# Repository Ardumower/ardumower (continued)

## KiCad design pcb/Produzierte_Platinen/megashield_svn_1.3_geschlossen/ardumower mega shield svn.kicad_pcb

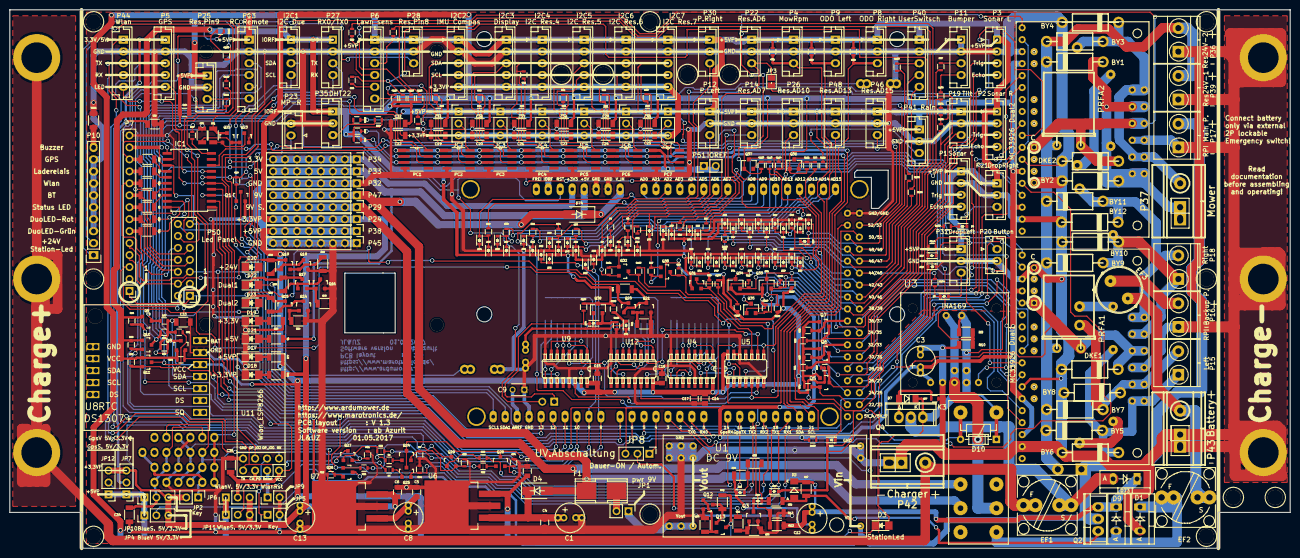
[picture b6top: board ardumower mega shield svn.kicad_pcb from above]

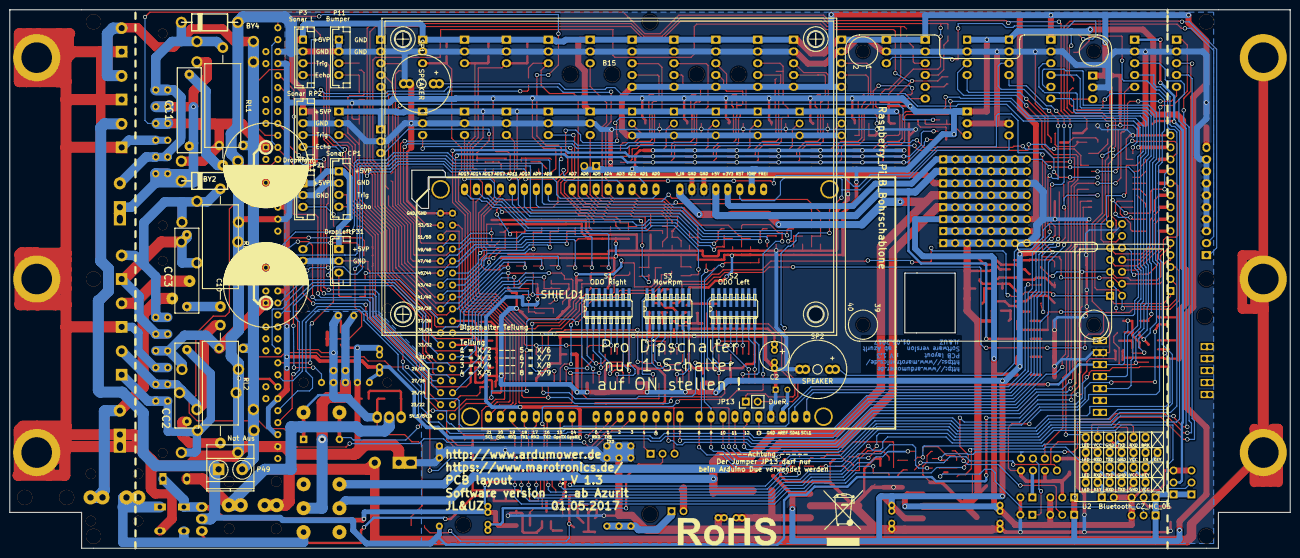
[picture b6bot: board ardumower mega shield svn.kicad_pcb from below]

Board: 2 copper layers, 271.8 x 114.3 mm, 442 parts (21 on the bottom side), 281 nets.

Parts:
B1, B2, B3, B4, B5, B6, B7, B8, B17, B18, B19, B20, B21, B22: Bohrloch_3,2mm
B9, B10, B11, B12, B13, B14: Bohrloch_6,5mm
B15: BumperDuino_Bohrschablone
B16: Raspberry_Pi_B_Bohrschablone; Raspberry_Pi_B_Bohrschablone_Rueckseite
B23: Mülleimer; WEEE-Logo_8.4x12mm_SilkScreen
B24: Rohos; RoHS-Logo_6mm_SilkScreen
BY1, BY2, BY3, BY4, BY5, BY6, BY7, BY8, BY9, BY10, BY11, BY12: BY 500/1000; Diode_liegend_BY500_1000_RM15
C1, C8, C13: 22uF; Elko_vert_11.2x6.3mm_RM2.5_RM5.0
C2: 47uF; Elko_vert_11.2x6.3mm_RM2.5_RM5.0
C3: 10uF; Elko_vert_11.2x6.3mm_RM2.5_RM5.0
C4, C5, C6, C7, C14, C15, C16, C17, C18: 100nF; C_0805
C9: 100nF; C_Disc_D3_P2.5
C10, C11: 2200uF 63V; C_Radial_D18_L36_P7.5
C12: 22uF / 63V; Elko_vert_11.2x6.3mm_RM2.5_RM5.0
C19, C20, C21, C22, C23, C24, C25, C26, C27, C28, C29, C30, C31, C32, C33, C34, C35, C36: 100nF; C_1206
CC1, CC2, CC3: MP3-Y2 10N; Kondensator_cnp_18x5mm
D1, D9: MBR 1045; Diode_TO-220_Vertical
D2, D7: SMD ZF 15; MiniMELF_Standard
D3: StationLed; LED_1206
D4, D74: S 1G SMD; D_SMA_Standard
D5, D6, D8, D11, D12, D13, D14, D15, D16, D24, D25, D26, D27, D28, D29, D30, D31, D32, D33, D34, D35, D36, D37, D38, D39, D40, D41, D42, D43, D44, D45, D46, D47, D48, D49, D50, D51, D52, D53, D54, D55, D56, D57, D58, D59, D60, D61, D62, D63, D64, D65, D66, D67, D68, D69, D70, D71, D72, D75, D76: TSS0230LU; D_0603
D10: 1N4148; D_DO-35_SOD27_P7.62mm_Horizontal
D17: +5VP; LED_1206
D18: +3,3VP; LED_1206
D19: +3,3V; LED_1206
D20: +24V; LED_1206
D21: +5V; LED_1206
D22: Dual1; LED_1206
D23: Dual2; LED_1206
D73: MBR 1045; MBR1045
DKE1, DKE2: 15KE33CA; Diode_liegend_BY500_1000_RM15
Dual1, Dual2: MC33926; MC_33926_31polig_mit_Bohrloch_neue_Masse_mit_zweite_Lochrei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
EF1: F_5A; Fuseholder5x20_vert_closed_Bulgin_FX0456_und_TR15_Halter
EF2: F_10A; Fuseholder5x20_vert_closed_Bulgin_FX0456_und_TR15_Halter
EF3: 1A; Sicherungs_Sockel_für_TR5_TE5
F1: PTC; Fuse_SMD
I2C1: I2C Due; JST_EH_B04B-EH-A_04x2.50mm_Straight
I2C2: IMU Compas; JST_EH_B05B-EH-A_05x2.50mm_Straight
I2C3: Display; JST_EH_B05B-EH-A_05x2.50mm_Straight
I2C4: I2C Res.4; JST_EH_B05B-EH-A_05x2.50mm_Straight
I2C5: I2C Res.5; JST_EH_B05B-EH-A_05x2.50mm_Straight
I2C6: I2C Res.6; JST_EH_B05B-EH-A_05x2.50mm_Straight
I2C7: I2C Res.7; JST_EH_B05B-EH-A_05x2.50mm_Straight
IC1: UDN 2987 LWTR-6T; SOIC-20W_7.5x12.8mm_Pitch1.27mm
JC2, JC3, JC4, JC5, JC6, JC7: JUMPER3; Pin_Header_Straight_1x03_Pitch2.54mm
JP1: pwr 9V; Pin_Header_Straight_1x02_Pitch2.54mm
JP2, JP5: Key; Pin_Header_Straight_1x02_Pitch2.54mm
JP3: M1FB; SJ
JP4: BlueV 5V/3.3V; Pin_Header_Straight_1x03_Pitch2.54mm
JP6: WlanV. 5V/3.3V; Pin_Header_Straight_1x03_Pitch2.54mm
JP7: GpsV 5V/3.3V; Pin_Header_Straight_1x03_Pitch2.54mm
JP8: UV.Abschaltung; Pin_Header_Straight_1x03_Pitch2.54mm
JP9: WlanRst; Pin_Header_Straight_1x02_Pitch2.54mm
JP10: BlueS. 5V/3.3V; Pin_Header_Straight_1x03_Pitch2.54mm
JP11: WlanS. 5V/3.3V; Pin_Header_Straight_1x03_Pitch2.54mm
JP12: GpsS. 5V/3.3V; Pin_Header_Straight_1x03_Pitch2.54mm
JP13: DueR.; Pin_Header_Straight_1x02_Pitch2.54mm
K3: RELAY_2RT; Relais_DPDT_Schrack-RT2_RM5mm_3D_Kontaktbelegung_geändert_F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
P1: Sonar C; JST_EH_B04B-EH-A_04x2.50mm_Straight
P2: Sonar R; JST_EH_B04B-EH-A_04x2.50mm_Straight
P3: Sonar L; JST_EH_B04B-EH-A_04x2.50mm_Straight
P4: MowRpm; JST_EH_B03B-EH-A_03x2.50mm_Straight
P5: GPS; JST_EH_B05B-EH-A_05x2.50mm_Straight
P6: Lawn sens; JST_EH_B06B-EH-A_06x2.50mm_Straight
P7: Status LEDs; Socket_Strip_Straight_1x14_Pitch2.54mm
P8: ODO Right; JST_EH_B03B-EH-A_03x2.50mm_Straight
P9: ODO Left; JST_EH_B03B-EH-A_03x2.50mm_Straight
P10: Status LEDs GND; Socket_Strip_Straight_1x10_Led_Bargraph_Anzeige
P11: Bumper; JST_EH_B04B-EH-A_04x2.50mm_Straight
P12: P.Left; JST_EH_B03B-EH-A_03x2.50mm_Straight
P13: RC Remote; JST_EH_B06B-EH-A_06x2.50mm_Straight
P14: Res.AD7; JST_EH_B03B-EH-A_03x2.50mm_Straight
P15: Left; TerminalBlock_Pheonix_MKDS1.5-2pol
P16: RPI Backup P.; TerminalBlock_Pheonix_MKDS1.5-2pol
P17: RPI Main P.; TerminalBlock_Pheonix_MKDS1.5-2pol
P18: Right; TerminalBlock_Pheonix_MKDS1.5-2pol
P19: Tilt; JST_EH_B03B-EH-A_03x2.50mm_Straight
P20: Button; JST_EH_B02B-EH-A_02x2.50mm_Straight
P21: DropRight; JST_EH_B03B-EH-A_03x2.50mm_Straight
P22: Res.AD6; JST_EH_B03B-EH-A_03x2.50mm_Straight
P23: MP-R; JST_EH_B02B-EH-A_02x2.50mm_Straight
P24: +3.3VP; Pin_Header_Straight_1x08_Pitch2.54mm
P25: Res.Pin9; JST_EH_B03B-EH-A_03x2.50mm_Straight
P26: Res.AD10; JST_EH_B03B-EH-A_03x2.50mm_Straight
P27: RX0/TX0; JST_EH_B04B-EH-A_04x2.50mm_Straight
P28: Res.Pin8; JST_EH_B03B-EH-A_03x2.50mm_Straight
P29: 9V S.; Pin_Header_Straight_1x08_Pitch2.54mm
P30: P.Right; JST_EH_B03B-EH-A_03x2.50mm_Straight
P31: DropLeft; JST_EH_B03B-EH-A_03x2.50mm_Straight
P32, P45: GND; Pin_Header_Straight_1x08_Pitch2.54mm
P33: 5V; Pin_Header_Straight_1x08_Pitch2.54mm
P34: 3,3V; Pin_Header_Straight_1x08_Pitch2.54mm
P35: DHT22; JST_EH_B03B-EH-A_03x2.50mm_Straight
P36: Res24V-2; TerminalBlock_Pheonix_MKDS1.5-2pol
P37: Mower; Anschlussklemme_RM5,08-RM7,62
P38: +5VP; Pin_Header_Straight_1x08_Pitch2.54mm
P39: Res24V-1; TerminalBlock_Pheonix_MKDS1.5-2pol
P40: UserSwitsch; JST_EH_B05B-EH-A_05x2.50mm_Straight
P41: Rain; JST_EH_B03B-EH-A_03x2.50mm_Straight
P42: Charger; Anschlussklemme_RM5,08-RM7,62
P43: Battery; Anschlussklemme_RM5,08-RM7,62
P44: Wlan; JST_EH_B05B-EH-A_05x2.50mm_Straight
P46: Res.AD15; JST_EH_B03B-EH-A_03x2.50mm_Straight
P47: 9V; Pin_Header_Straight_1x08_Pitch2.54mm
P48: Res.AD13; JST_EH_B03B-EH-A_03x2.50mm_Straight
P49: Not Aus; TerminalBlock_Pheonix_MKDS1.5-2pol
P50: Led Panel; Pin_Header_Straight_2x07_Pitch2.54mm
P51: IOREF; Socket_Strip_Straight_1x02_Pitch2.54mm
PC1, PC2, PC3, PC4, PC5, PC6, PC7: PCA9517D; SOIC127P600X175-8N
PRFA1, PRFA2: PFRA 500; PRFA_500
Q1, Q24, Q25, Q26, Q27, Q28, Q29, Q38: BC847B; SOT-23
Q2, Q4: IRF9540N; TO-220
Q3, Q12, Q13, Q14, Q15, Q16, Q17, Q18, Q19, Q20, Q21, Q22, Q23: BC817; SOT-23
Q5, Q6, Q7, Q8, Q9, Q10, Q11, Q30, Q31, Q32, Q33, Q34, Q35, Q36, Q37: BSS138; SOT-23
R1, R2, R5, R17, R20, R21, R22, R25, R77, R134: 220R; R_1206
R3, R4, R26, R27, R29, R50, R54, R82, R83, R84, R85, R86, R87, R88, R89, R90, R103, R104, R105, R106, R107, R108, R109, R110, R111, R112: 300R; R_0603
R6, R7, R16, R28, R30, R31, R92, R93, R96: 4K7; R_0603
R8, R14, R15, R39, R42, R46, R49, R51, R52, R53, R55, R56, R58, R59, R60, R61, R62, R63, R64, R65, R66, R67, R68, R69, R70, R71, R91, R94, R95, R97, R98, R99, R100, R101, R102, R113, R114, R115, R116, R117, R118, R119, R120, R121, R122, R123, R124, R131, R132, R133, R137: 10K; R_0603
R9, R12: 100K 0,1%; R_1206
R10, R13: 10K 0,1%; R_1206
R11, R73, R79: 68R; R_1206
R18, R43: 2k2; R_0603
R19, R38, R72, R74, R76, R81: 8K2; R_1206
R23, R33, R78: 100R; R_1206
R24, R75, R80: 180R; R_1206
R32: 1K; R_1206
R34, R35: 10K; R_1206
R36: 30K; R_1206
R37: 100K; R_1206
R40, R41, R44, R45, R47, R48, R125, R126, R127, R128, R129, R130: XXXX; R_0603
R57: 100K; R_0603
R135: 56K; R_0603
R136: 1K; R_0603
RL1, RL2, RL3: 1,8R 2W METALL; Resistor_Horizontal_RM25mm-2W
S1: ODO Right; SW_DIP_x8_SMD
S2: ODO Left; SW_DIP_x8_SMD
S3: MowRpm; SW_DIP_x8_SMD
SHIELD1: ARDUINO_MEGA_SHIELD; ARDUINO_MEGA_SHIELD_DUO_3D
SP1, SP2: SPEAKER; Buzzer_12x9.5RM7.6_RM5.0
U1: DC 9V; DC_DC_DSN2596_mit_Bohrloch_doppelte_Lochreihe
U2: Bluetooth_CZ_HC_05; Bluetooth_Buchse_Platz_mit_Beschriftung_4_fach
U3: INA169
U4, U9, U12: 4017; 40xx-SO16
U5: 4081; 40xx-SO14
U6: LM2940CS-5.0; TO-263-3Lead
U7: LM3940IS-3.3; TO-263-3Lead
U8: DS1307+; Tiny_RTC_DS1307_geändert_mit_Bohrloch_4Lochreihen
U11: Wlan_ESP8266; Wlan_ESP8266_3D_mit_Pin_Beschreibung_ohne_Rahmen

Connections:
9Vgeschaltet: K3.3, P29.1, P29.2, P29.3, P29.4, P29.5, P29.6, P29.7, P29.8
+3.3VP: C6.1, C13.1, I2C2.5, I2C3.5, I2C4.5, I2C5.5, I2C6.5, I2C7.5, JC2.3, JC3.3, JC4.3, JC5.3, JC6.3, JC7.3, JP2.2, JP4.3, JP6.3, JP7.3, JP10.3, JP11.3, JP12.3, P24.1, P24.2, P24.3, P24.4, P24.5, P24.6, P24.7, P24.8, R78.1, U7.3
+3V3: P34.1, P34.2, P34.3, P34.4, P34.5, P34.6, P34.7, P34.8, R23.1, SHIELD1.3V3
+5V: P33.1, P33.2, P33.3, P33.4, P33.5, P33.6, P33.7, P33.8, R1.1, SHIELD1.5V
+5VP: C5.1, C7.1, C8.1, C14.1, C15.1, C16.1, C17.1, C18.1, C22.1, C33.1, I2C2.1, I2C3.1, I2C4.1, I2C5.1, I2C6.1, I2C7.1, IC1.11, JC2.1, JC3.1, JC4.1, JC5.1, JC6.1, JC7.1, JP4.1, JP6.1, JP7.1, JP10.1, JP11.1, JP12.1, P1.1, P2.1, P3.1, P4.1, P6.1, P8.1, P9.1, P12.1, P13.1, P14.1, P19.1, P21.1, P22.1, P25.1, P26.1, P28.1, P30.1, P31.1, P38.1, P38.2, P38.3, P38.4, P38.5, P38.6, P38.7, P38.8, P40.1, P41.1, P46.1, P48.1, PC1.8, R28.2, R30.2, R31.1, R43.1, R59.1, R61.1, R63.1, R65.1, R67.1, R69.1, R71.1, R77.1, R98.1, R100.1, R102.1, R116.1, R118.1, R120.1, R122.1, R124.1, U4.16, U5.14, U6.3, U7.1, U8.3, U9.16, U12.16
+9V: D4.2, D74.2, F1.2, K3.5, P47.1, P47.2, P47.3, P47.4, P47.5, P47.6, P47.7, P47.8
+24V: D20.2, P7.5, P17.2, P49.1, P50.5, Q2.2, U1.3
/Anschlußstecker/LShifter1/5V_IN: P1.4, Q5.3, R59.2
/Anschlußstecker/LShifter2/5V_IN: P2.4, Q6.3, R61.2
/Anschlußstecker/LShifter3/5V_IN: P3.4, Q7.3, R63.2
/Anschlußstecker/LShifter4/5V_IN: P13.3, Q8.3, R65.2
/Anschlußstecker/LShifter5/5V_IN: P13.4, Q9.3, R67.2
/Anschlußstecker/LShifter6/5V_IN: P13.5, Q10.3, R69.2
/Anschlußstecker/LShifter7/5V_IN: P13.6, Q11.3, R71.2
/Anschlußstecker/LShifter8/5V_IN: Q30.3, R98.2, U5.10
/Anschlußstecker/LShifter9/5V_IN: Q31.3, R100.2, U5.4
/Anschlußstecker/LShifter10/5V_IN: Q32.3, R102.2, U5.3
/Anschlußstecker/LShifter11/5V_IN: P3.3, Q33.3, R116.2
/Anschlußstecker/LShifter12/5V_IN: P2.3, Q34.3, R118.2
/Anschlußstecker/LShifter13/5V_IN: P1.3, Q35.3, R120.2
/Anschlußstecker/LShifter14/5V_IN: P41.3, Q36.3, R122.2
/Anschlußstecker/LShifter15/5V_IN: P19.3, Q37.3, R124.2
/Anschlußstecker/OdoTeiler/Eingang1: P8.3, R28.1, U4.14, U5.1
/Anschlußstecker/OdoTeiler/Eingang2: P9.3, R30.1, U5.5, U9.14
/Anschlußstecker/OdoTeiler/Eingang3: P4.3, R31.2, U5.8, U12.14
/Motortreiber/+24V: BY1.1, BY3.1, BY5.1, BY7.1, BY9.1, BY11.1, P36.2, P39.2, P49.2, PRFA1.1, PRFA2.1
/Motortreiber/MotorLinks/MotorIN1: BY5.2, BY6.1, CC2.1, Dual1.19, P15.1
/Motortreiber/MotorLinks/MotorIN2: BY7.2, BY8.1, Dual1.20, P15.2, RL2.2
/Motortreiber/MotorRechts/MotorIN1: BY9.2, BY10.1, CC3.1, Dual1.23, P18.1
/Motortreiber/MotorRechts/MotorIN2: BY11.2, BY12.1, Dual1.24, P18.2, RL3.2
/Motortreiber/MähmotorSchutz/MotorIN1: BY1.2, BY2.1, CC1.1, Dual2.19, Dual2.23, P37.1
/Motortreiber/MähmotorSchutz/MotorIN2: BY3.2, BY4.1, Dual2.20, Dual2.24, P37.2, RL1.2
/USpannungAB/Batterieeingang 24V: C12.1, D2.1, D9.1, D73.1, Q2.3, R12.1, R37.1
/VerpolungsschutzLade./Eingang: D73.2, EF1.2, Q4.2
Charg_Pin_+: B9.1, B10.1, B11.1, EF1.1, P42.2
DHT22: P35.3, R39.2, R109.1
DropLeft: D5.1, P31.3
DropRight: D6.1, P21.3
Dual1: C10.1, D22.2, DKE1.1, Dual1.22, PRFA1.2
Dual2: C11.1, D23.2, DKE2.1, Dual2.22, PRFA2.2
DuoLED-Rot: IC1.2, SHIELD1.7
DuoLED_Grün: IC1.1, SHIELD1.6
GND: B12.1, B13.1, B14.1, BY2.2, BY4.2, BY6.2, BY8.2, BY10.2, BY12.2, C1.2, C2.2, C3.2, C4.2, C5.2, C6.2, C7.2, C8.2, C9.1, C10.2, C11.2, C13.2, C14.2, C15.2, C16.2, C17.2, C18.2, C19.2, C20.2, C21.2, C22.2, C23.2, C24.2, C25.2, C26.2, C27.2, C28.2, C29.2, C30.2, C31.2, C32.2, C33.2, C34.2, C35.2, C36.2, D1.2, D16.2, D17.1, D18.1, D19.1, D21.1, D24.2, D25.2, D27.2, D30.2, D34.2, D35.2, D36.2, D38.2, D40.2, D42.2, D44.2, D46.2, D48.2, D50.2, D52.2, D54.2, D56.2, D58.2, D60.2, D62.2, D64.2, D66.2, D68.2, D70.2, D72.2, D75.2, DKE1.2, DKE2.2, Dual1.2, Dual1.7, Dual1.16, Dual1.21, Dual2.2, Dual2.7, Dual2.16, Dual2.21, I2C1.2, I2C2.2, I2C3.2, I2C4.2, I2C5.2, I2C6.2, I2C7.2, IC1.12, JP5.2, JP9.2, P1.2, P2.2, P3.2, P4.2, P5.2, P6.2, P7.14, P8.2, P9.2, P10.3, P10.4, P10.5, P10.6, P10.7, P10.8, P10.9, P11.1, P11.2, P12.2, P13.2, P14.2, P16.1, P17.1, P19.2, P20.2, P21.2, P22.2, P23.2, P25.2, P26.2, P27.2, P28.2, P30.2, P31.2, P32.1, P32.2, P32.3, P32.4, P32.5, P32.6, P32.7, P32.8, P35.2, P36.1, P39.1, P40.2, P41.2, P42.1, P43.1, P44.2, P45.1, P45.2, P45.3, P45.4, P45.5, P45.6, P45.7, P45.8, P46.2, P48.2, P50.14, PC1.4, PC2.4, PC3.4, PC4.4, PC5.4, PC6.4, PC7.4, Q1.2, Q3.2, Q12.2, Q14.2, Q16.2, Q18.2, Q21.2, Q23.2, R8.2, R10.2, R11.2, R13.2, R14.2, R15.2, R24.2, R35.2, R57.2, R73.2, R75.2, R79.2, R80.2, R91.2, R94.2, R95.2, R134.2, R136.2, SHIELD1.GND1, SHIELD1.GND2, SHIELD1.GND3, SHIELD1.GND4, SHIELD1.GND5, SP1.1, SP2.1, U1.1, U1.4, U2.GND, U3.2, U4.8, U4.13, U5.7, U5.12, U5.13, U6.2, U6.4, U7.2, U7.4, U8.2, U9.8, U9.13, U11.GND, U12.8, U12.13
GPS-LED: IC1.7, P5.5
GPS_RX: Q28.2, R94.1, SHIELD1.14
GPS_TX: R96.2, SHIELD1.15
IOREF: C3.1, C26.1, C27.1, C28.1, C29.1, C30.1, C31.1, C32.1, D8.1, D11.1, D26.1, D28.1, D29.1, D31.1, D32.1, D33.1, D37.1, D39.1, D41.1, D43.1, D45.1, D47.1, D49.1, D51.1, D53.1, D55.1, D57.1, D59.1, D61.1, D63.1, D65.1, D67.1, D69.1, D71.1, Dual1.3, Dual1.6, Dual1.15, Dual2.3, Dual2.6, Dual2.15, I2C1.1, JP8.3, P27.1, P35.1, P51.1, P51.2, PC1.1, PC2.1, PC3.1, PC4.1, PC5.1, PC6.1, PC7.1, Q5.1, Q6.1, Q7.1, Q8.1, Q9.1, Q10.1, Q11.1, Q24.3, Q25.3, Q28.3, Q30.1, Q31.1, Q32.1, Q33.1, Q34.1, Q35.1, Q36.1, Q37.1, Q38.3, R39.1, R47.1, R48.1, R58.1, R60.1, R62.1, R64.1, R66.1, R68.1, R70.1, R97.1, R99.1, R101.1, R113.2, R114.2, R115.1, R117.1, R119.1, R121.1, R123.1, R125.2, R126.2, R127.2, R128.2, R129.2, R130.2, R131.2, R132.2, R133.2, R135.1, R137.2, SHIELD1.IORE, U3.1
Led-BT: IC1.4, U2.LED
Led-Status: IC1.3, SHIELD1.13
Led-Wlan: IC1.5, P44.5, U11.GP_2
unnamed: C1.1, C4.1, D4.1, U6.1
unnamed: C2.1, D75.1, Q38.1, R135.2
unnamed: C9.2, SHIELD1.AREF
unnamed: C12.2, D12.2, R34.1
unnamed: C19.1, JC2.2, PC2.8, R40.1, R44.1
unnamed: C20.1, JC3.2, PC3.8, R41.1, R45.1
unnamed: C21.1, JC4.2, PC4.8, R42.1, R46.1
unnamed: C23.1, JC5.2, PC5.8, R51.1, R55.1
unnamed: C24.1, JC6.2, PC6.8, R52.1, R56.1
unnamed: C25.1, JC7.2, PC7.8, R49.1, R53.1
unnamed: C34.1, JP4.2, U2.VCC
unnamed: C35.1, JP6.2, P44.1, U11.CH_P, U11.VCC
unnamed: C36.1, JP7.2, P5.1
unnamed: CC1.2, RL1.1
unnamed: CC2.2, RL2.1
unnamed: CC3.2, RL3.1
unnamed: D1.1, D9.2, EF2.1, K3.16
unnamed: D2.2, Q2.1, R32.2, R37.2
unnamed: D3.1, Q13.3, R72.1
unnamed: D5.2, R104.1
unnamed: D6.2, R103.1
unnamed: D7.2, Q4.1, R57.1
unnamed: D10.2, K3.9, Q1.3
unnamed: D11.2, D24.1, R3.2, SHIELD1.AD5
unnamed: D12.1, R33.1, R34.2
unnamed: D13.2, D15.2, R32.1, R33.2
unnamed: D15.1, Q3.3
unnamed: D8.2, D16.1, R4.2, SHIELD1.AD4
unnamed: D17.2, R77.2
unnamed: D18.2, R78.2
unnamed: D19.2, R23.2
unnamed: D20.1, Q19.3, R76.1
unnamed: D21.2, R1.2
unnamed: D22.1, Q17.3, R38.1
unnamed: D23.1, Q15.3, R19.1
unnamed: D25.1, D26.2, R103.2, R114.1, SHIELD1.23
unnamed: D27.1, D28.2, R110.2, SHIELD1.35
unnamed: D29.2, D30.1, R87.2, R132.1, SHIELD1.38
unnamed: D31.2, D34.1, R105.2, R131.1, SHIELD1.39
unnamed: D32.2, D35.1, R111.2, R129.1, SHIELD1.9
unnamed: D33.2, D36.1, R112.2, R130.1, SHIELD1.8
unnamed: D37.2, D38.1, R29.2, R126.1, SHIELD1.40
unnamed: D39.2, D40.1, R54.2, R125.1, SHIELD1.41
unnamed: D41.2, D42.1, R83.2, R128.1, SHIELD1.42
unnamed: D43.2, D44.1, R85.2, R127.1, SHIELD1.43
unnamed: D45.2, D46.1, R86.2, SHIELD1.44
unnamed: D47.2, D48.1, R104.2, R113.1, SHIELD1.45
unnamed: D49.2, D50.1, R108.2, SHIELD1.47
unnamed: D51.2, D52.1, R106.2, SHIELD1.46
unnamed: D53.2, D54.1, R26.2, SHIELD1.AD7
unnamed: D55.2, D56.1, R82.2, SHIELD1.AD6
unnamed: D57.2, D58.1, R109.2, SHIELD1.49
unnamed: D59.2, D60.1, R84.2, SHIELD1.AD2
unnamed: D61.2, D62.1, R107.2, SHIELD1.48
unnamed: D63.2, D64.1, R90.2, SHIELD1.AD8
unnamed: D65.2, D66.1, R27.2, SHIELD1.AD15
unnamed: D67.2, D68.1, R89.2, SHIELD1.AD9
unnamed: D69.2, D70.1, R50.2, SHIELD1.AD13
unnamed: D71.2, D72.1, R88.2, SHIELD1.AD10
unnamed: D74.1, SHIELD1.V_IN
unnamed: D76.1, Q38.2, R136.1
unnamed: D76.2, JP13.1, R137.1
unnamed: Dual2.9, JP3.2
unnamed: EF2.2, EF3.1, P43.2
unnamed: EF3.2, P16.2
unnamed: F1.1, JP1.2
unnamed: IC1.10, R43.2
unnamed: IC1.13, P7.13, P50.13, SP1.2, SP2.2
unnamed: IC1.14, R25.1
unnamed: IC1.15, R17.1
unnamed: IC1.16, R22.1
unnamed: IC1.17, R2.1
unnamed: IC1.18, R5.1
unnamed: IC1.19, R20.1
unnamed: IC1.20, R21.1
unnamed: JP1.1, U1.2
unnamed: JP2.1, U2.Key
unnamed: JP5.1, U11.GP_0
unnamed: JP8.2, R36.2
unnamed: JP9.1, U11.Rese
unnamed: JP10.2, Q26.3
unnamed: JP11.2, Q27.3
unnamed: JP12.2, Q29.3
unnamed: K3.12, U3.5
unnamed: P5.3, R93.2
unnamed: P5.4, Q29.2, R95.1
unnamed: P7.2, P10.1, P50.2, Q22.3, R81.1
unnamed: P7.3, P10.2, P50.3, Q20.3, R74.1
unnamed: P10.10, R134.1
unnamed: P44.3, R7.2, U11.TX
unnamed: P44.4, Q27.2, R91.1, U11.RX
unnamed: P7.6, P50.6, R21.2
unnamed: P7.7, P50.7, R20.2
unnamed: P7.8, P50.8, R5.2
unnamed: P7.9, P50.9, R2.2
unnamed: P7.10, P50.10, R22.2
unnamed: P7.11, P50.11, R17.2
unnamed: P7.12, P50.12, R25.2
unnamed: Q1.1, R18.2
unnamed: Q3.1, R35.1, R36.1
unnamed: Q12.1, Q13.2, R73.1
unnamed: Q12.3, Q13.1, R72.2
unnamed: Q14.1, Q15.2, R24.1
unnamed: Q14.3, Q15.1, R19.2
unnamed: Q16.1, Q17.2, R75.1
unnamed: Q16.3, Q17.1, R38.2
unnamed: Q18.1, Q19.2, R80.1
unnamed: Q18.3, Q19.1, R76.2
unnamed: Q20.1, Q21.3, R74.2
unnamed: Q20.2, Q21.1, R11.1
unnamed: Q22.1, Q23.3, R81.2
unnamed: Q22.2, Q23.1, R79.1
unnamed: Q24.1, R6.1
unnamed: Q25.1, R7.1
unnamed: Q26.1, R16.1
unnamed: Q26.2, R15.1, U2.RXD
unnamed: Q27.1, R92.1
unnamed: Q28.1, R93.1
unnamed: Q29.1, R96.1
unnamed: R6.2, U2.TXD
unnamed: S1.1, U4.4
unnamed: S1.2, U4.7
unnamed: S1.3, U4.10
unnamed: S1.4, U4.1
unnamed: S1.5, U4.5
unnamed: S1.6, U4.6
unnamed: S1.7, U4.9
unnamed: S1.8, U4.11
unnamed: S1.9, S1.10, S1.11, S1.12, S1.13, S1.14, S1.15, S1.16, U4.15
unnamed: S2.1, U9.4
unnamed: S2.2, U9.7
unnamed: S2.3, U9.10
unnamed: S2.4, U9.1
unnamed: S2.5, U9.5
unnamed: S2.6, U9.6
unnamed: S2.7, U9.9
unnamed: S2.8, U9.11
unnamed: S2.9, S2.10, S2.11, S2.12, S2.13, S2.14, S2.15, S2.16, U9.15
unnamed: S3.1, U12.4
unnamed: S3.2, U12.7
unnamed: S3.3, U12.10
unnamed: S3.4, U12.1
unnamed: S3.5, U12.5
unnamed: S3.6, U12.6
unnamed: S3.7, U12.9
unnamed: S3.8, U12.11
unnamed: S3.9, S3.10, S3.11, S3.12, S3.13, S3.14, S3.15, S3.16, U12.15
unnamed: U4.2, U5.2
unnamed: U5.6, U9.2
unnamed: U5.9, U12.2
RX0: P27.3, SHIELD1.0
RX1: Q25.2, R14.1, SHIELD1.19
RX2: Q24.2, R8.1, SHIELD1.17
RelaisAbschaltung: JP8.1, SHIELD1.4
ReserveAD6: JP3.1, P22.3, R82.1
ReserveAD7: P14.3, R26.1
ReserveAD10: P26.3, R88.1
ReservePin8: P28.3, R112.1
ReservePin9: P25.3, R111.1
Reset: JP13.2, P23.1, SHIELD1.RST
Resv.PinAD13: P48.3, R50.1
Resv.PinAD15: P46.3, R27.1
SCL: PC1.2, PC2.2, PC3.2, PC4.2, PC5.2, PC6.2, PC7.2, R48.2, SHIELD1.21
SCL1: PC1.7, U8.5
SCL2: I2C2.4, PC2.7, R44.2
SCL3: I2C3.4, PC3.7, R45.2
SCL4: I2C4.4, PC4.7, R46.2
SCL5: I2C5.4, PC5.7, R51.2
SCL6: I2C6.4, PC6.7, R52.2
SCL7: I2C7.4, PC7.7, R49.2
SCL22: I2C1.4, SHIELD1.SCL1
SDA: PC1.3, PC2.3, PC3.3, PC4.3, PC5.3, PC6.3, PC7.3, R47.2, SHIELD1.20
SDA1: PC1.6, U8.4
SDA2: I2C2.3, PC2.6, R40.2
SDA3: I2C3.3, PC3.6, R41.2
SDA4: I2C4.3, PC4.6, R42.2
SDA5: I2C5.3, PC5.6, R55.2
SDA6: I2C6.3, PC6.6, R56.2
SDA7: I2C7.3, PC7.6, R53.2
SDA22: I2C1.3, SHIELD1.SDA1
StationLed: D3.2, D7.1, D10.1, K3.8, P7.4, P50.4, Q4.3, R9.1, U3.4
TX0: P27.4, SHIELD1.1
TX1: R92.2, SHIELD1.18
TX2: R16.2, SHIELD1.16
Taster: D13.1, D14.1, P7.1, P20.1, P50.1
pinBatteryVoltage: R12.2, R13.1, R84.1
pinBumperLeft: P11.4, R105.1
pinBumperRight: P11.3, R87.1
pinButton: D14.2, R133.1, SHIELD1.51
pinBuzzer: IC1.8, SHIELD1.53
pinChargeCurrent: R90.1, U3.3
pinChargeVoltage: R9.2, R10.1, R89.1
pinChargingEnable: IC1.6, R18.1, SHIELD1.50
pinLawnBackRecv: P6.6, R83.1
pinLawnBackSend: P6.5, R85.1
pinLawnFrontRecv: P6.4, R29.1
pinLawnFrontSend: P6.3, R54.1
pinMotorEnable: Dual1.10, SHIELD1.37
pinMotorLeftDir: Dual1.4, SHIELD1.31
pinMotorLeftFault: Dual1.8, SHIELD1.25
pinMotorLeftPWM: Dual1.5, SHIELD1.5
pinMotorLeftSense: Dual1.9, SHIELD1.AD1
pinMotorMowDir: Dual2.4, Dual2.13, SHIELD1.29
pinMotorMowEnable: Dual2.10, SHIELD1.28
pinMotorMowFault: Dual2.8, Dual2.17, SHIELD1.26
pinMotorMowPWM: Dual2.5, Dual2.14, SHIELD1.2
pinMotorMowRpm_neu: Q30.2, R97.2, SHIELD1.AD11
pinMotorMowSense: Dual2.18, SHIELD1.AD3
pinMotorRightDir: Dual1.13, SHIELD1.33
pinMotorRightFault: Dual1.17, SHIELD1.27
pinMotorRightPWM: Dual1.14, SHIELD1.3
pinMotorRightSense: Dual1.18, SHIELD1.AD0
pinOdometryLeft: Q31.2, R99.2, SHIELD1.AD12
pinOdometryRight: Q32.2, R101.2, SHIELD1.AD14
pinPerimeterLeft: P12.3, R3.1
pinPerimeterRight: P30.3, R4.1
pinRain: Q36.2, R86.1, R121.2
pinRemoteMow: Q8.2, R64.2, SHIELD1.12
pinRemoteSpeed: Q10.2, R68.2, SHIELD1.10
pinRemoteSteer: Q9.2, R66.2, SHIELD1.11
pinRemoteSwitch: Q11.2, R70.2, SHIELD1.52
pinSonarCenterEcho: Q5.2, R58.2, SHIELD1.22
pinSonarCenterTrigger: Q35.2, R119.2, SHIELD1.24
pinSonarLeftEcho: Q7.2, R62.2, SHIELD1.36
pinSonarLeftTrigger: Q33.2, R115.2, SHIELD1.34
pinSonarRightEcho: Q6.2, R60.2, SHIELD1.32
pinSonarRightTrigger: Q34.2, R117.2, SHIELD1.30
pinTilt: Q37.2, R110.1, R123.2
pinUserSwitch1: P40.5, R106.1
pinUserSwitch2: P40.4, R108.1
pinUserSwitch3: P40.3, R107.1

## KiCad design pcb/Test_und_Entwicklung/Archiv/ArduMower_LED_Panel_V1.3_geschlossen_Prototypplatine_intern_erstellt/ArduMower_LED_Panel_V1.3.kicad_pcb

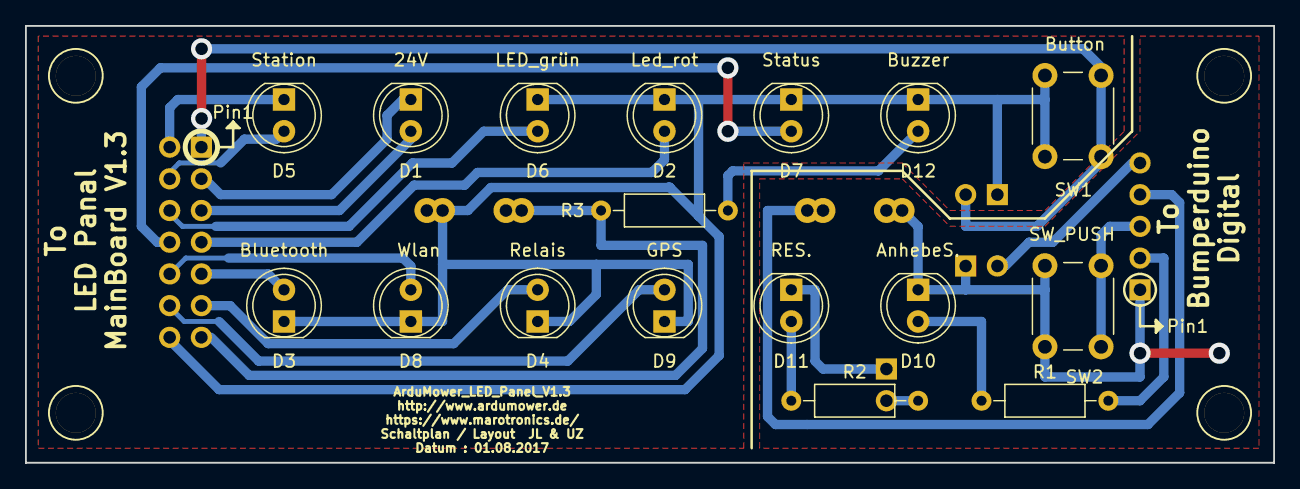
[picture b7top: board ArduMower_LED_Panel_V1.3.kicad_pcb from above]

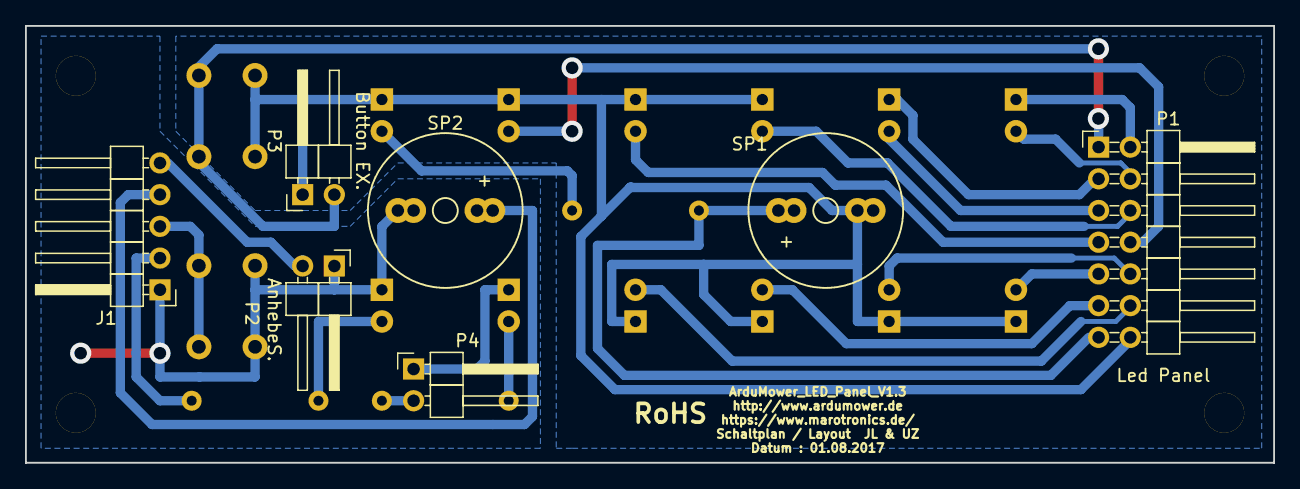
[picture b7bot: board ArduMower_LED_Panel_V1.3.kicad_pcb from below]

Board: 2 copper layers, 100.0 x 35.0 mm, 28 parts (7 on the bottom side), 24 nets.

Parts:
B1, B2, B3, B4: Bohrloch_3,2mm_ohne_Kupferfläche; Bohrloch_3,2mm
D1: 24V; LED_D5.0mm
D2: Led_rot; LED_D5.0mm
D3: Bluetooth; LED_D5.0mm
D4: Relais; LED_D5.0mm
D5: Station; LED_D5.0mm
D6: LED_grün; LED_D5.0mm
D7: Status; LED_D5.0mm
D8: Wlan; LED_D5.0mm
D9: GPS; LED_D5.0mm
D10: AnhebeS.; LED_D5.0mm
D11: RES.; LED_D5.0mm
D12: Buzzer; LED_D5.0mm
J1: CONN_01X05; Pin_Header_Angled_1x05_Pitch2.54mm
P1: Led Panel; Pin_Header_Angled_2x07_Pitch2.54mm
P2: AnhebeS.; Pin_Header_Angled_1x02_Pitch2.54mm
P3: Button EX.; Pin_Header_Angled_1x02_Pitch2.54mm
P4: RES.; Pin_Header_Angled_1x02_Pitch2.54mm
R1, R2, R3: 220; R_Axial_DIN0207_L6.3mm_D2.5mm_P10.16mm_Horizontal
SP1: Buzzer; Buzzer_12x9.5RM7.6_RM5.0
SP2: SPEAKER; Buzzer_12x9.5RM7.6_RM5.0
SW1: Button; SW_PUSH_6mm_h8.5mm
SW2: SW_PUSH; SW_PUSH_6mm_h8.5mm

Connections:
/24V: D1.2, P1.5
/24V_GND: D1.1, P1.3
/Bluetooth: D3.2, P1.9
/Buzzer: P1.13, R3.2, SP1.2
/Duo_Led_Rot: D2.2, P1.7
/Duo_Led_grün: D6.2, P1.6
/GPS_LED: D9.2, P1.12
/Led_Status: D7.2, P1.8
/PinCharging_Enable: D4.2, P1.11
/StationLed: D5.2, P1.4
/StationLed_GND: D5.1, P1.2
/Taster: P1.1, P3.2, SW1.2
/Wlan: D8.2, P1.10
GND: D2.1, D3.1, D4.1, D6.1, D7.1, D8.1, D9.1, D12.1, P1.14, P3.1, SP1.1, SW1.1
GNDD: D10.1, J1.1, P2.1, SP2.1, SW2.1
unnamed: D10.2, R1.1
unnamed: D11.1, P4.1
unnamed: D11.2, R2.1
unnamed: D12.2, R3.1
unnamed: J1.2, R1.2
unnamed: J1.3, SW2.2
unnamed: J1.4, SP2.2
unnamed: J1.5, P2.2
unnamed: P4.2, R2.2
